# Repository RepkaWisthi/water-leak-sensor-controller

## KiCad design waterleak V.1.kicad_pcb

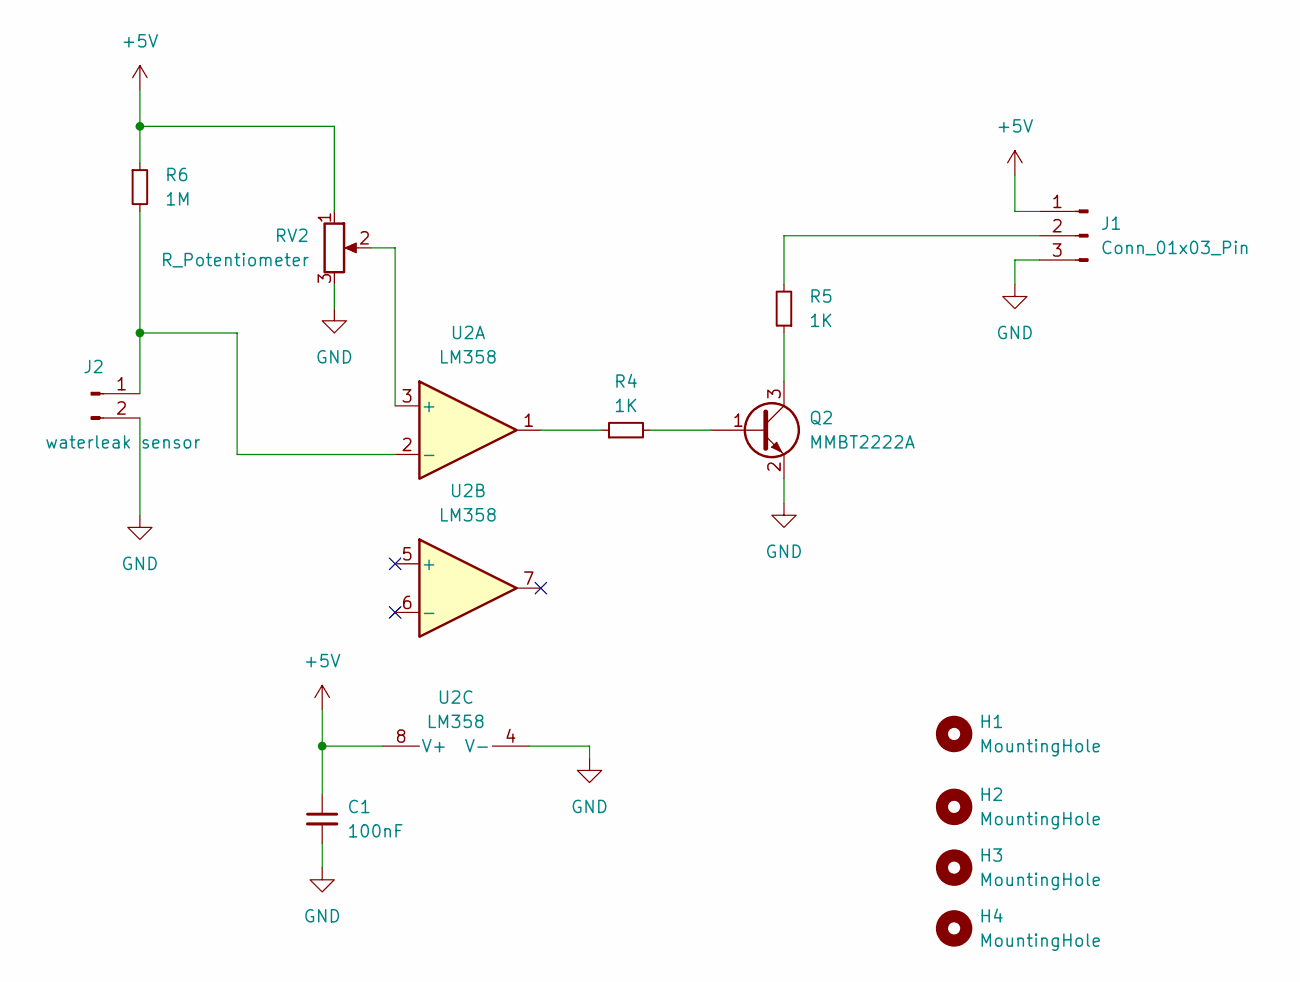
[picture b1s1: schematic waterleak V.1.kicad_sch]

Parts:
C1: 100nF; C_0805_2012Metric_Pad1.18x1.45mm_HandSolder
H1, H2, H3, H4: MountingHole; MountingHole_3.2mm_M3_Pad_Via
J1: Conn_01x03_Pin; TerminalBlock_4Ucon_1x03_P3.50mm_Horizontal
J2: waterleak sensor; TerminalBlock_4Ucon_1x02_P3.50mm_Horizontal
Q2: MMBT2222A; SOT-23
R4, R5: 1K; R_0805_2012Metric_Pad1.20x1.40mm_HandSolder
R6: 1M; R_0805_2012Metric_Pad1.20x1.40mm_HandSolder
RV2: R_Potentiometer; Potentiometer_Bourns_3296W_Vertical
U2: LM358; SOP-8_3.9x4.9mm_P1.27mm

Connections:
+5V: C1.1, J1.1, R6.1, RV2.1, U2.8 (V+)
GND: C1.2, J1.3, J2.2, Q2.2 (E), RV2.3, U2.4 (V-)
unnamed: J1.2, R5.2
unnamed: J2.1, R6.2, U2.2 (-)
unnamed: Q2.1 (B), R4.2
unnamed: Q2.3 (C), R5.1
unnamed: R4.1, U2.1
unnamed: RV2.2, U2.3 (+)

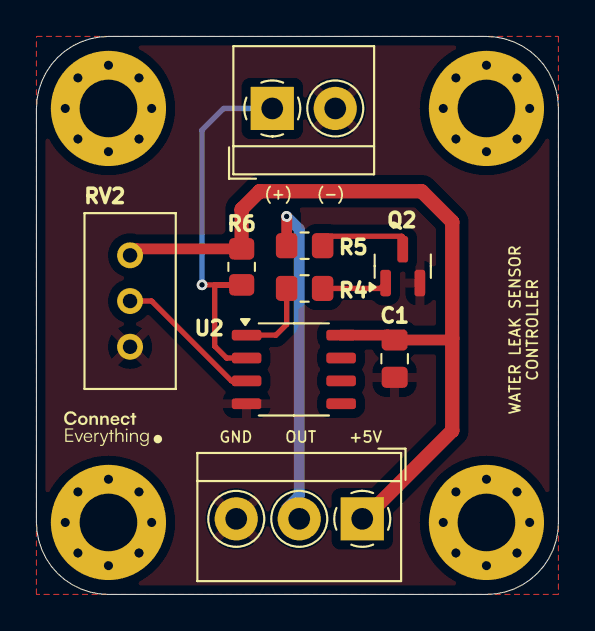
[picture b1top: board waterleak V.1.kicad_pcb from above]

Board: 2 copper layers, 29.0 x 31.0 mm, 13 parts (0 on the bottom side), 8 nets.

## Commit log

2024-08-01 water-leak-sensor
2024-08-01 upload testing
2024-08-02 add gerber
